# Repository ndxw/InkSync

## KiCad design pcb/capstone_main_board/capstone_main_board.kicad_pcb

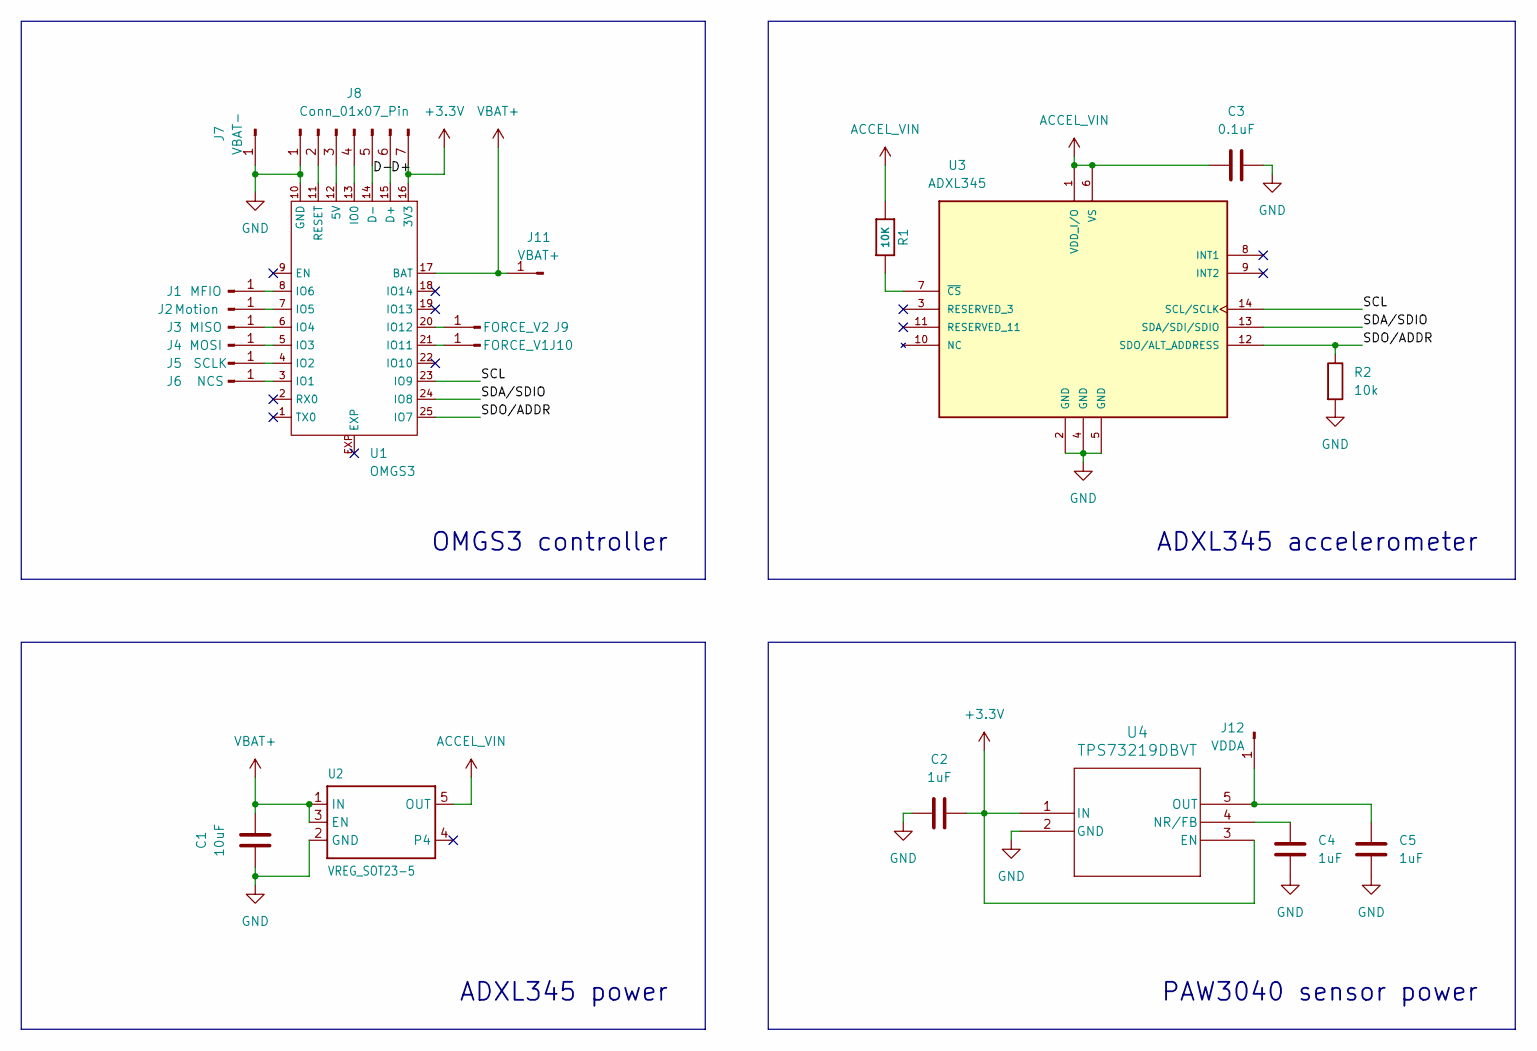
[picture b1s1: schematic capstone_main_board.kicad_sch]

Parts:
C1: 10uF; C_0805_2012Metric
C2, C4, C5: 1uF; C_0603_1608Metric
C3: 0.1uF; C_0402_1005Metric
J1: MFIO; PinHeader_1x01_P2.00mm_Vertical
J2: Motion; PinHeader_1x01_P2.00mm_Vertical
J3: MISO; PinHeader_1x01_P2.00mm_Vertical
J4: MOSI; PinHeader_1x01_P2.00mm_Vertical
J5: SCLK; PinHeader_1x01_P2.00mm_Vertical
J6: NCS; PinHeader_1x01_P2.00mm_Vertical
J7: VBAT-; PinHeader_1x01_P2.00mm_Vertical
J8: Conn_01x07_Pin; OMGS3_programming_pins
J9: FORCE_V2; PinHeader_1x01_P2.00mm_Vertical
J10: FORCE_V1; PinHeader_1x01_P2.00mm_Vertical
J11: VBAT+; PinHeader_1x01_P2.00mm_Vertical
J12: VDDA; PinHeader_1x01_P2.00mm_Vertical
R1: 10K; R_0402_1005Metric
R2: 10k; R_0402_1005Metric
U1: OMGS3
U2: VREG_SOT23-5; SOT95P280X145-5N
U3: ADXL345; PQFN80P500X300X100-14N; PARTREV B
U4: TPS73219DBVT; DBV5_TEX

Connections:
+3.3V: C2.1, J8.7, U1.16 (3V3), U4.1 (IN), U4.3 (EN)
/D+: J8.6, U1.15 (D+)
/D-: J8.5, U1.14 (D-)
/SCL: U1.23 (IO9), U3.14 (SCL/SCLK)
/SDA/SDIO: U1.24 (IO8), U3.13 (SDA/SDI/SDIO)
/SDO/ADDR: R2.1, U1.25 (IO7), U3.12 (SDO/ALT_ADDRESS)
ACCEL_VIN: C3.2, R1.2, U2.5 (OUT), U3.1 (VDD_I/O), U3.6 (VS)
GND: C1.1, C2.2, C3.1, C4.2, C5.2, J7.1, J8.1, R2.2, U1.10 (GND), U2.2 (GND), U3.2 (GND), U3.4 (GND), U3.5 (GND), U4.2 (GND)
unnamed: J1.1, U1.8 (IO6)
unnamed: J2.1, U1.7 (IO5)
unnamed: J3.1, U1.6 (IO4)
unnamed: J4.1, U1.5 (IO3)
unnamed: J5.1, U1.4 (IO2)
unnamed: J6.1, U1.3 (IO1)
unnamed: J8.2, U1.11 (RESET)
unnamed: J8.3, U1.12 (5V)
unnamed: J8.4, U1.13 (IO0)
unnamed: J9.1, U1.20 (IO12)
unnamed: J10.1, U1.21 (IO11)
unnamed: C5.1, J12.1, U4.5 (OUT)
unnamed: R1.1, U3.7 (~CS)
unnamed: C4.1, U4.4 (NR/FB)
VBAT+: C1.2, J11.1, U1.17 (BAT), U2.1 (IN), U2.3 (EN)

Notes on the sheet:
PAW3040 sensor power
OMGS3 controller
ADXL345 accelerometer
ADXL345 power

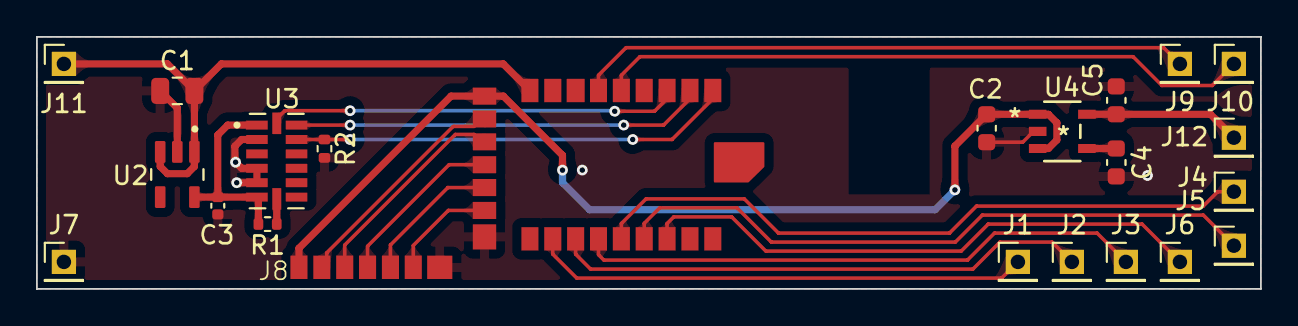
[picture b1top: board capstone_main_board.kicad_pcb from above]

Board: 2 copper layers, 68.0 x 14.0 mm, 23 parts (0 on the bottom side), 23 nets.

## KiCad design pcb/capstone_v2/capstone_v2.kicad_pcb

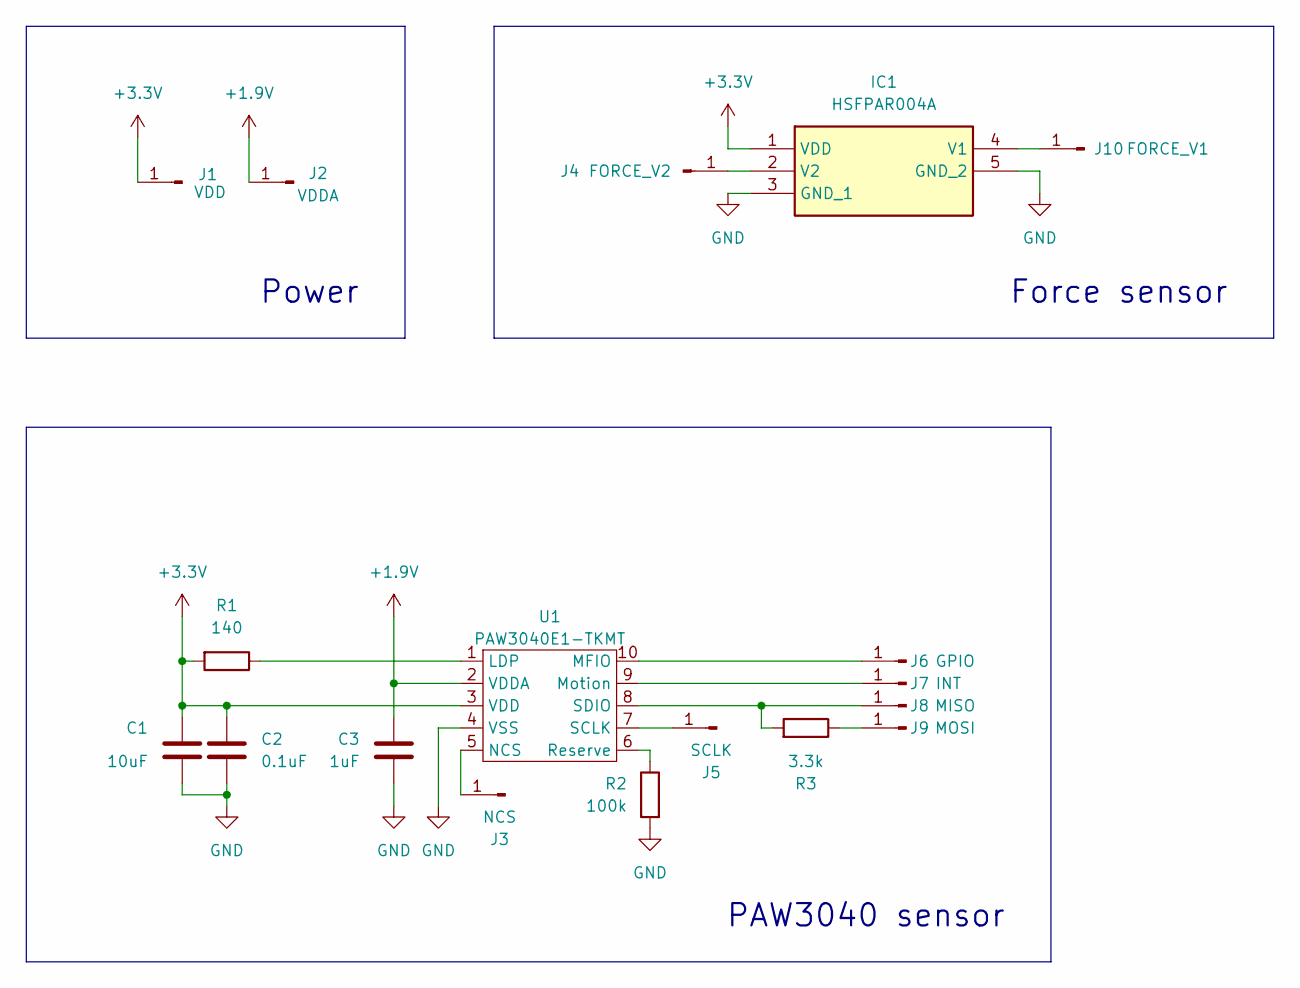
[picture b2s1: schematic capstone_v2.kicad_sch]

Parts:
C1: 10uF; C_0805_2012Metric
C2: 0.1uF; C_0402_1005Metric
C3: 1uF; C_0603_1608Metric
IC1: HSFPAR004A; Mouser Part Number 688-HSFPAR004A
J1: VDD; PinHeader_1x01_P1.00mm_Vertical
J2: VDDA; PinHeader_1x01_P1.00mm_Vertical
J3: NCS; PinHeader_1x01_P1.00mm_Vertical
J4: FORCE_V2; PinHeader_1x01_P1.00mm_Vertical
J5: SCLK; PinHeader_1x01_P1.00mm_Vertical
J6: GPIO; PinHeader_1x01_P1.00mm_Vertical
J7: INT; PinHeader_1x01_P1.00mm_Vertical
J8: MISO; PinHeader_1x01_P1.00mm_Vertical
J9: MOSI; PinHeader_1x01_P1.00mm_Vertical
J10: FORCE_V1; PinHeader_1x01_P1.00mm_Vertical
R1: 140; R_0603_1608Metric
R2: 100k; R_0603_1608Metric
R3: 3.3k; R_0402_1005Metric
U1: PAW3040E1-TKMT

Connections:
+1.9V: C3.1, J2.1, U1.2 (VDDA)
+3.3V: C1.1, C2.1, IC1.1 (VDD), J1.1, R1.2, U1.3 (VDD)
GND: C1.2, C2.2, C3.2, IC1.3 (GND_1), IC1.5 (GND_2), R2.2, U1.4 (VSS)
unnamed: IC1.4 (V1), J10.1
unnamed: IC1.2 (V2), J4.1
unnamed: J3.1, U1.5 (NCS)
unnamed: J5.1, U1.7 (SCLK)
unnamed: J6.1, U1.10 (MFIO)
unnamed: J7.1, U1.9 (Motion)
unnamed: J8.1, R3.2, U1.8 (SDIO)
unnamed: J9.1, R3.1
unnamed: R1.1, U1.1 (LDP)
unnamed: R2.1, U1.6 (Reserve)

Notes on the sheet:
PAW3040 sensor
Force sensor
Power

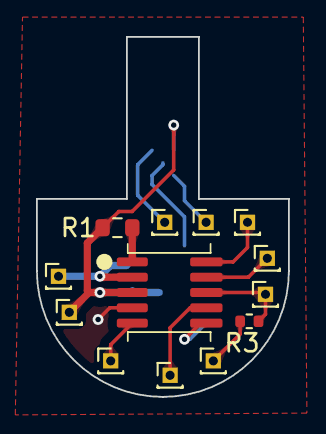
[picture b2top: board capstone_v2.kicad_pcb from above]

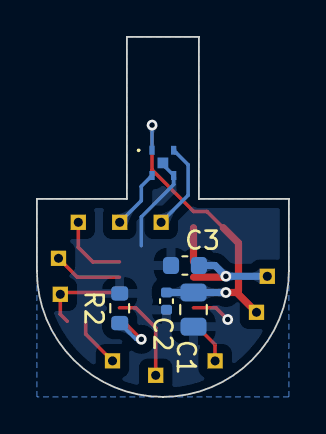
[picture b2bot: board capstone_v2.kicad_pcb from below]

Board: 2 copper layers, 14.0 x 20.0 mm, 18 parts (5 on the bottom side), 13 nets.

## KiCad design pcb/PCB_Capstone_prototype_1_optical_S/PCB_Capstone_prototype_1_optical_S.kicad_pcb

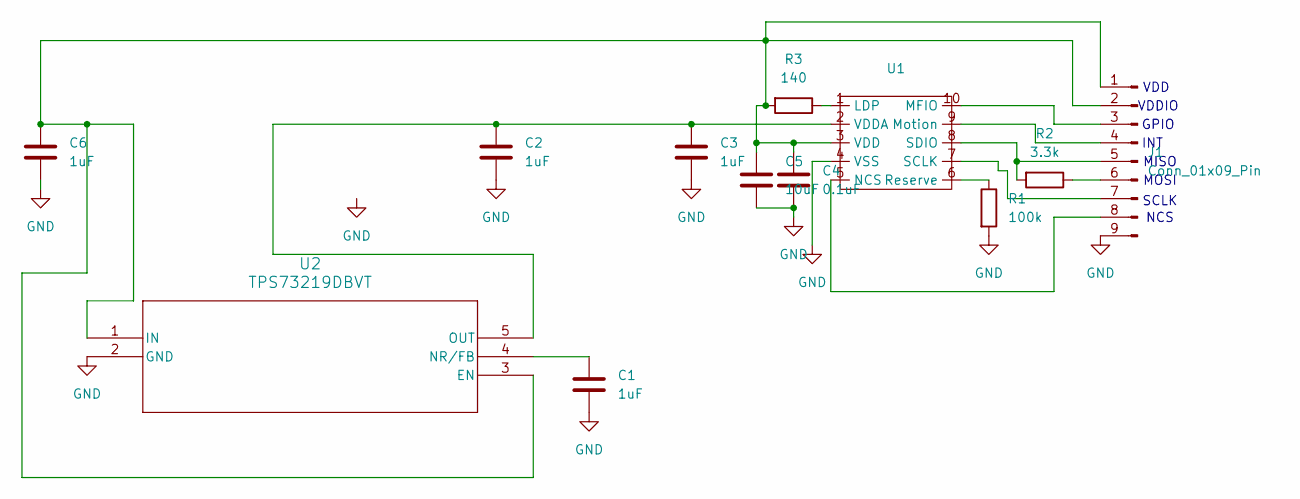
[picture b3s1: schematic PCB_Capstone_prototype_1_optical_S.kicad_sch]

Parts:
C1, C2, C3, C6: 1uF; CAP_CL10_SAM
C4: 0.1uF; CAP_CL05_SAM
C5: 10uF; CAP_CL21_SAM
J1: Conn_01x09_Pin; PinHeader_1x09_P1.00mm_Vertical
R1: 100k; RC0603N_PAN
R2: 3.3k; RC0603N_PAN
R3: 140; RC0603N_PAN
U1: Optical_Sensor
U2: TPS73219DBVT; DBV5_TEX

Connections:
GND: C1.2, C2.2, C3.2, C4.2, C5.2, C6.2, J1.9, R1.2, U1.4 (VSS), U2.2 (GND)
unnamed: C4.1, C5.1, C6.1, J1.1, J1.2, R3.2, U1.3 (VDD), U2.1 (IN), U2.3 (EN)
unnamed: J1.3, U1.10 (MFIO)
unnamed: J1.4, U1.9 (Motion)
unnamed: J1.5, R2.2, U1.8 (SDIO)
unnamed: J1.6, R2.1
unnamed: J1.7, U1.7 (SCLK)
unnamed: J1.8, U1.5 (NCS)
unnamed: R3.1, U1.1 (LDP)
unnamed: R1.1, U1.6 (Reserve)
unnamed: C2.1, C3.1, U1.2 (VDDA), U2.5 (OUT)
unnamed: C1.1, U2.4 (NR/FB)

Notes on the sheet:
SCLK
MISO
INT
VDD
MOSI
NCS
VDDIO
GPIO

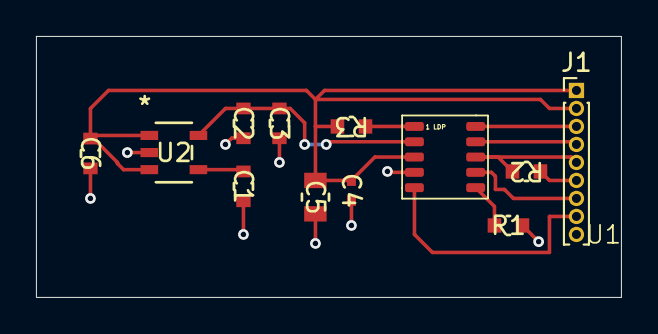
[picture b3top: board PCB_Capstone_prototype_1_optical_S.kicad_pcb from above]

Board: 2 copper layers, 32.5 x 14.5 mm, 12 parts (0 on the bottom side), 12 nets.

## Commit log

2024-12-12 BLE test
2025-01-11 added directories
2025-01-12 Uploaded design files for optical sensor
2025-01-14 unzipped pcb
2025-01-14 committed mouse recording script
2025-01-28 update git ignore
2025-02-03 attempting SPI communication
2025-02-08 debug using SPI bitbanging
2025-02-14 successful read from all three sensors
2025-02-14 finished initOpticalSensor function
2025-02-20 enclosure
2025-03-12 messing with HID report descriptor
2025-03-15 sensor and mcu board v1
2025-03-16 sensor and mcu board nearly complete
2025-03-16 removed irrelevant kicad projects
2025-03-16 untracked .zip
2025-03-16 added teardrops
2025-03-22 enclosure main body complete
2025-03-25 optical sensor done
2025-03-25 programming jig
2025-03-25 initial shell design
2025-03-26 completed enclosure top half
2025-03-26 refactored
2025-03-30 force sensor test
2025-04-03 Fixed pressure and absolute movement
2025-04-08 Polished code and added comments
2025-04-20 created drawings for report
